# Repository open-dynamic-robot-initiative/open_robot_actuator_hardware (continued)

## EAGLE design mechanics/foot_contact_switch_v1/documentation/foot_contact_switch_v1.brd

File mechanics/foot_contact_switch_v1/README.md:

# Foot Contact Switch v1
 <br>*Working principle of the optical foot contact switch*

## Description
We designed simple, low cost, lightweight and robust optical foot contact switch for our [quadruped robot.](../quadruped_robot_8dof_v1#quadruped-robot-8dof-v1)  
The contact switch consists of a spring loaded aperture that is located between a led light source and a light sensor.  
External loads displace the aperture and change the light intensity measured by the sensor.  
For centering the foot we use 12 elastic silicone elements (6 on each side).

The foot contact switch is symmetric and can detect forces from a wide range of different angles (270 degrees).  
For visual feedback and monitoring there are bi-color leds mounted on each side of the foot.

<br>*Left side: Foot Contact Switch loaded / Right side: Foot Contact Switch unloaded*

## Lower Leg and Foot Contact Switch
 <br>*Lower Leg and Foot Contact Switch Component Overview*

 <br>*Lower Leg and Foot Contact Switch assembled - weight: 35g*

The weight of the foot, the contact switch electronics and the silicone elements is about 10g.  
To prevent the foot from rotating we use a steel pin that is guided by the lower leg structure.   
Under load the foot deflects up to 2mm from its neutral position.  
The electronics are supplied with 3.3V and generate an analog output signal between 3V and 0V.  
The signal is converted by the microcontroller ADC and transmitted over CAN at 1kHz.  
We measured the delay of the foot contact switch with respect to a ATI Mini40 force sensor for a drop of the 2dof leg from a height of 8cm.   
The measured delay between the ATI force sensor signal and the foot contact signal was 2ms.  
The data was logged at 1kHz using a Realtime Linux PC.

<br>*Foot Contact Switch Electronics*

## Video

## Sensor Characteristics
 <br>
* x-axis -> vertical force [N] measured with ATI Mini40 Sensor  
* y-axis -> foot contact sensor ouput signal inverted and normalized
* 0-1 on the y-axis corresponds to 3V - 0V range

## Off-the-shelf Components
### Silicone Tube
<br>

* Silicone tube - outer diameter: 6mm / inner diameter: 4mm / length: 3mm  
* 12 elements / 6 on each side
* a [tube cutter](../actuator_module_v1/details/details_tools.md#tube-cutter) can be used to prepare the segments

### Bicycle Tire
<br>

* a bicycle tire segment is bonded to the surface of the foot
* we use Schwalbe Lugano 28" 23-622 tire
* cut to 65mm x 10mm pieces
* bond to the foot with [Loctite 406](../actuator_module_v1/details/details_tools.md#loctite)
* [Instructions Foot Preparation](../general/lower_legs.md#preparing-the-lower-legs)

### Fasteners
<br>

* Steel Pin 1,5mm x 12mm  
* Socket Head Cap Screws M2,5x6
* Helicoil Thread Inserts M2,5 x 3.75mm

## 3D Printed Parts
 <br>

`The recommended printing direction for all the parts below is the positive z direction of the stl files.`

The STL files for 3d printing the parts are available in the [STL folder](stl_files).

 <br>
* [Lower Leg Structure Base - 18g](stl_files/lower_leg_structure_base.STL)
* FDM or SLS printer

 <br>
* [Lower Leg Structure Fork - 5g](stl_files/lower_leg_structure_fork.STL)
* FDM or SLS printer

 <br>
* [Foot Structure - 3.4g](stl_files/foot_structure.STL)
* SLA printer - Accura Extreme Gray

## Custom Electronic Boards
The foot contact switch consists of two boards with traces and components on all four sides.  
The diameter of the electronics boards is 10mm.  

 <br>*Foot Contact Switch Main Board  - Left: Outer side / Right: Inner Side*

 <br>*Foot Contact Switch Satellite Board  - Left: Outer side / Right: Inner Side*

## Light Sensor Offset
 <br>*Picture Light Sensor - the sensitive area is not in the center of the component*
* note that the sensing area of the light sensor is not in the geometrical center of the component
* when we solder the light sensor we use a microscope to align the sensing area of the sensor with the center of the board

## Switching Voltage for the Indicator Leds
 <br>*Schematic - voltage divider for switching the indicator leds*

* the switching voltage for the indicator leds on the foot is set by the voltage divider R4 and R5
* we use 10kΩ for R4 and 20kΩ for R5 resulting in a switching voltage of 2.2V
* you can adjust the switching voltage by changing the ratio of the voltage divider
* the switching voltage threshold is only used for the indicator leds
* the microcontroller receives the full range analog signal
* that means that you can set the threshold on the software side independently

## Details Foot Contact Switch
Special thanks to Joshi Walzog for designing and manufacturing the electronics boards!

* [Bill Of Materials Foot Contact Switch - PDF Document](documentation/bom_foot_contact_switch_v1.pdf)
* [Bill Of Materials - Excel Document](documentation/bom_foot_contact_switch_v1.xlsx)  
* [Eagle Files - Zipped Folder](documentation/eagle_files.zip)
* [Gerber Files - Zipped Folder](documentation/gerber_files.zip)

To view the Eagle files you need to download the free [Eagle PCB Design Software](https://www.autodesk.com/products/eagle/free-download#) for Windows, Mac and Linux.

## Foot Contact Switch Wiring
 <br>*Foot Contact Switch Connectors and Wiring*

## Alternative Lower Leg Versions

 <br>  

* alternative lower leg versions without contact sensor are documented here: [Lower Leg Documentation](../general/lower_legs.md#lower-legs)

## PDF Drawing
<br> *Foot Contact Switch Overview - Click on the picture to view the PDF drawing*

## View the foot contact switch cad model in your web browser
<br> *Foot Contact Switch - Click on the picture to view the cad model in your browser*

## More Information
[Open Dynamic Robot Initiative - Webpage](https://open-dynamic-robot-initiative.github.io)  
[Open Dynamic Robot Initiative - YouTube Channel](https://www.youtube.com/channel/UCx32JW2oIrax47Gjq8zNI-w)   
[Open Dynamic Robot Initiative - Forum](https://odri.discourse.group/categories)  
[Open Dynamic Robot Initiative - Paper](https://arxiv.org/pdf/1910.00093.pdf)  
[Hardware Overview](../../README.md#open-robot-actuator-hardware)  
[Software Overview](https://github.com/open-dynamic-robot-initiative/open-dynamic-robot-initiative.github.io/wiki)  

## Authors
Felix Grimminger

## License
BSD 3-Clause License

## Copyright
Copyright (c) 2019-2022, Max Planck Gesellschaft and New York University

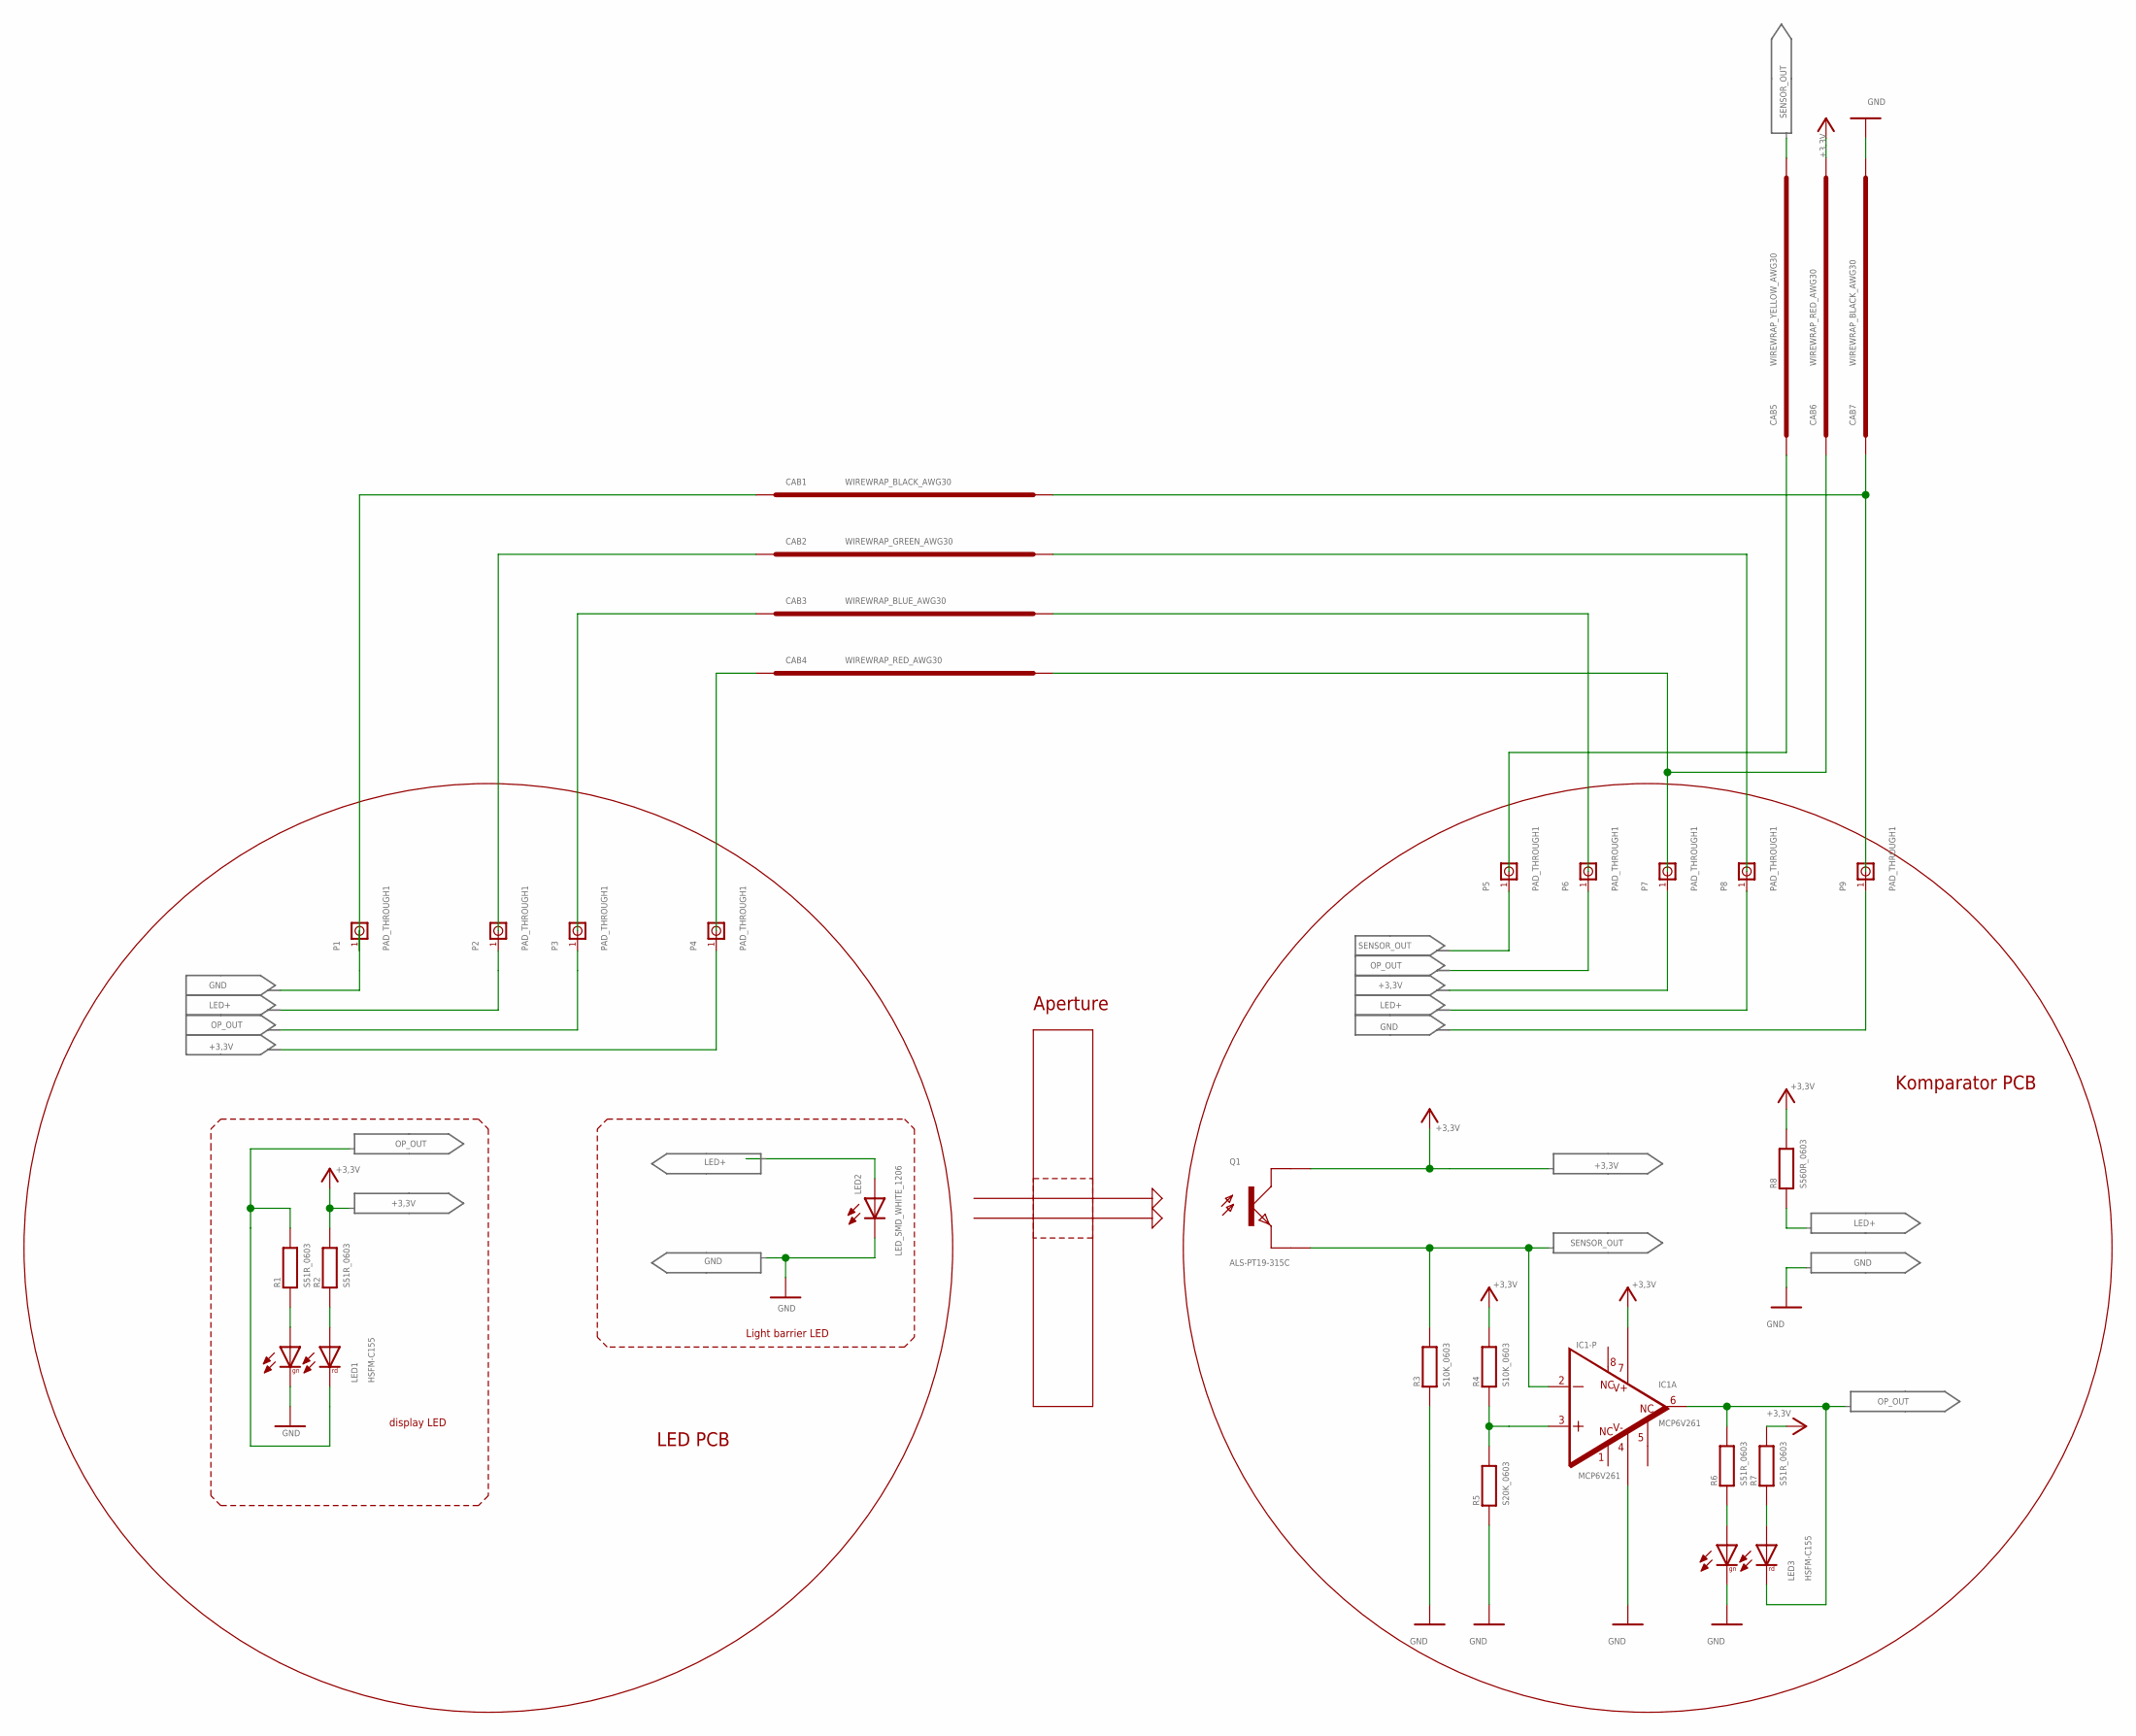
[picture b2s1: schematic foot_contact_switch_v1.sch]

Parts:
CAB1, CAB7: WIREWRAP_BLACK_AWG30; WIREWRAP_AWG30
CAB2: WIREWRAP_GREEN_AWG30; WIREWRAP_AWG30
CAB3: WIREWRAP_BLUE_AWG30; WIREWRAP_AWG30
CAB4, CAB6: WIREWRAP_RED_AWG30; WIREWRAP_AWG30
CAB5: WIREWRAP_YELLOW_AWG30; WIREWRAP_AWG30
IC1: MCP6V261; MSOP8
LED1, LED3: HSFM-C155; 3225
LED2: LED_SMD_WHITE_1206; 1206C
P1, P2, P3, P4, P5, P6, P7, P8, P9: PAD_THROUGH1; PAD_TH_056X055
Q1: ALS-PT19-315C; FOTOTRANSISTOR
R1, R2, R6, R7: S51R_0603; 0603R
R3, R4: S10K_0603; 0603R
R5: S20K_0603; 0603R
R8: S560R_0603; 0603R

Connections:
+3,3V: CAB6.7, IC1.7, P4.P$1, P7.P$1, Q1.1 (C), R2.P$2 (2), R4.P$2 (2), R7.P$2 (2), R8.P$2 (2)
GND: CAB7.7, IC1.4, LED1.2, LED2.- (C1), LED3.2, P1.P$1, P9.P$1, R3.P$1 (1), R5.P$1 (1)
LED+: LED2.+ (A1), P2.P$1, P8.P$1, R8.P$1 (1)
unnamed: IC1.3, R4.P$1 (1), R5.P$2 (2)
unnamed: CAB4.7, CAB6.1
unnamed: LED3.1, R6.P$1 (1)
unnamed: CAB1.7, CAB7.1
unnamed: LED3.3, R7.P$1 (1)
unnamed: LED1.1, R1.P$1 (1)
unnamed: LED1.3, R2.P$1 (1)
OP_OUT: IC1.6, LED1.4, LED3.4, P3.P$1, P6.P$1, R1.P$2 (2), R6.P$2 (2)
SENSOR_OUT: CAB5.7, IC1.2, P5.P$1, Q1.2 (E), R3.P$2 (2)

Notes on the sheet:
Aperture
LED PCB
Komparator PCB
display LED
Light barrier LED

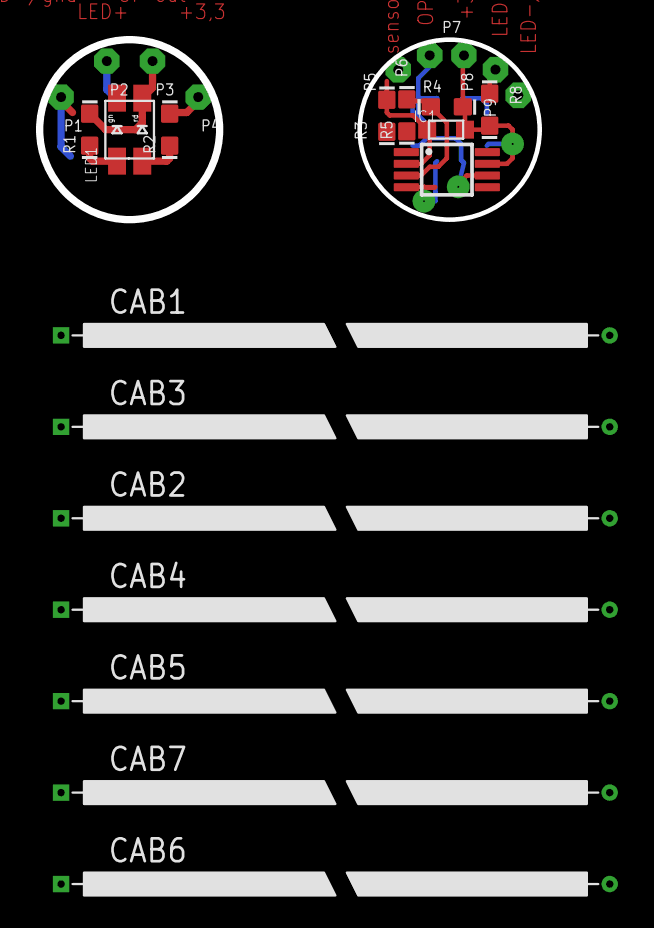
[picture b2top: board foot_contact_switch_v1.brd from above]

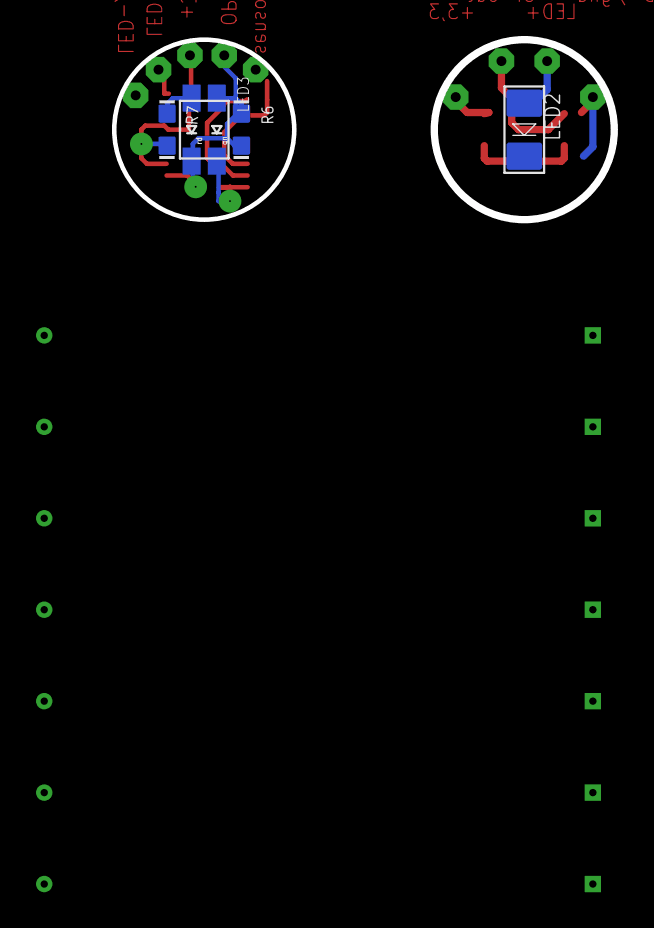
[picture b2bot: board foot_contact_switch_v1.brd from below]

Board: 2 copper layers, 29 parts (4 on the bottom side), 12 nets.

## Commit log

2019-08-20 Update LICENSE
2019-08-22 STL file upload
2019-09-03 Added actuator module description
2019-09-03 Updated documentation
2019-09-03 Update actuator module documentation
2019-09-04 Updating documentation
2019-09-10 Added detail information - 3d printed parts
2019-09-11 Updating documentation - print orientation 3d printed parts
2019-09-11 Updating 2dof leg documentation
2019-09-11 Updating documentation - foot contact switch
2019-09-12 Updating documentation - details actuator module
2019-09-12 Uploading technical drawings
2019-09-12 Updating documentation - machined parts
2019-09-12 Updating encoder codewheel documentation
2019-09-12 Fixing broken links
2019-09-18 Updating encoder documentation
2019-09-20 Updating wiring documentation
2019-09-30 Updating foot contact switch documentation
2019-09-30 Updating shell preparation and assembly documentation
2019-10-02 Adding video
2019-10-02 Uploading belt tensioner rollers different diameters
2019-10-02 Uploading tool for output pulley
2019-10-07 Updating lower leg documentation
2019-10-07 Fixing links
2019-10-08 Updating foot contact switch details
2019-10-08 Updating foot contact switch pictures
2019-10-10 Updating quadruped documentation
2019-10-10 Fixing link
2019-10-10 Fixing broken link
2019-10-10 Updating quadruped inertia parameters
2019-10-10 Linking cicle art video
2019-10-10 Uploading pictures
2019-10-21 Adding documentation - center pulley preparation
2019-10-21 Adding details - motor modification
2019-10-22 Updating documentation - center pulley preparation
2019-10-23 Adding tool documentation
2019-10-23 Adding detail pages - motor shaft and output pulley preparation
2019-10-24 Adding links to files
2019-10-25 Adding link to youtube channel
2019-10-30 Adding TI evaluation board information
2019-11-11 Updating tool documentation
2019-11-11 Adding Documentation - 3d printing orientation
2019-12-04 Added STL link for table attachment
2019-12-09 Adding documentation - simple lower leg
2019-12-13 Updating Micro Driver Documentation
2019-12-13 Updating MicroDriver documentation
2019-12-13 Basic outline for how to flash cards
2020-01-17 Adding pictures
2020-01-28 Adding documentation for udrive flashing
2020-01-28 Add German supplier for JTAG Emulator
2020-02-12 Uploading step files - machined parts
2020-02-12 Fixing broken links - software overview
2020-02-13 Adding images about jumper.
2020-02-13 Update the Flash the firmware part
2020-02-13 Upload images for CCS
2020-02-13 Import steps for running CSS debugger
2020-02-21 Testing
2020-02-21 Use markdown syntax for including images
2020-04-06 Adding links to encoder mount stl files
2020-04-27 Starting 12dof quadruped documentation
2020-04-28 Adding hip aa bearing information
2020-04-28 Uploading simplified Solo12 model for visualization
2020-05-04 Starting biped documentation
2020-05-04 Starting FingerEdu and TriFingerEdu documentation
2020-05-04 Documenting quadruped range of motion
2020-05-04 Updating navigation
2020-05-04 Removing duplicates
2020-05-06 Adding missing dimension
2020-05-08 Adding missing dimensions
2020-05-12 Uploading Hip AA Support Step File
2020-05-12 Uploading missing STL files
2020-05-12 Adding documentation - Body structure preparation and Vicon object
2020-05-13 Uploading step files
2020-05-19 Adding vicon object information for biped
2020-06-22 Updating documentation - electronic components
2020-06-24 Updating biped documentation
2020-06-24 Updating pictures
2020-06-26 Updating biped robot documentation
2020-06-26 Updating documentation - biped leg
2020-06-30 added stand_attachment FreeCAD model
    - not perfect reproduction of STL, some fillets are 0.5 instead of 1 mm
2020-07-02 Added FreeCAD CAD project files
    - body_structure_biped_right_side
    - micro_driver_stack_spacer
    Removed STL from stand_attachment
2020-07-06 Reinforcing electronics mount
2020-07-09 Updating documentation - leg test stand
2020-07-10 Updating footers
2020-07-16 Create iframe_test
2020-07-16 Update iframe_test
2020-07-16 Testing iFrame
2020-07-20 Updating documentation - bill of materials actuator module core
2020-07-21 Adding instructions for MicroDriver soldering
2020-07-21 Fix filenames
2020-07-22 MicroDriver: Rename image files
2020-07-24 Updating documentation - spi bus wiring
2020-07-24 Adding STL file - finger adapter
2020-07-28 added body_structure_biped_front freecad file
2020-08-03 Adding link to cad model for web browser
2020-08-03 Adding links to cad model for web browser
2020-08-03 Starting documentation - nyu finger
2020-08-05 Updating power connector ordering information
2020-08-10 Adding link- components and tools
2020-08-11 Updating sources for bearings
2020-08-12 Adding wiring documentation - Kabeltronik cables
2020-08-12 Moving shell stl files to 2dof leg
2020-08-12 Updating documentation - motor preparation
2020-08-13 Updating component information
2020-08-17 Updating drawings
2020-08-18 Updating documentation - encoder preparation
2020-08-18 Updating documentation - motor shaft preparation
2020-08-24 Updating documentation - step by step instructions
2020-08-26 Updating documentation - shell preparation
2020-08-31 Updating navigation - adding step by step instructions
2020-09-01 Updating codewheel ordering instructions
2020-09-21 Fixing view setting cad model
2020-09-30 Updating documentation - foot contact switch eagle and gerber files
2020-10-06 Uploading Solidworks files
2020-10-14 Updating step files
2020-10-15 Updating 8dof quadruped v2 documentation
2020-10-15 Updating docuementation
2020-10-16 Uploading wire edm drawings
2020-10-16 Replacing dxf file with zip file
2020-10-19 Uploading vicon top structure quadruped 8dof v2
2020-10-19 Uploading Solidworks files quadruped 8dof v1
2020-10-19 Uploading edrawing files
2020-10-20 Linking cad models for viewing in browser
2020-10-21 Updating documentation - quadruped 8dof v2 vicon object
2020-10-22 Updating documentation - quadruped 8dof v2
2020-10-26 Update documentation
2020-10-28 Correcting error in upper leg shell cover
2020-10-30 Updating documentation - 3dof leg
2020-11-25 Fixing navigation
2020-11-25 Updating documtentation
2020-11-25 added the alternative option for the 3d printed encoder codewheel
2020-11-25 Adding wiring documentation - 12dof quadruped
2020-11-27 Updating documentation - 12dof robot
2020-12-02 Update README.md
    Fixing a broken link to the Transmission Belt Tensioner Roller.
2020-12-03 Updating conventions
2020-12-11 Fixing broken links to stl parts
2021-01-15 Adding details to the actuator module assembly instructions
2021-01-18 added link for precision resistors
2021-01-20 Updating component and tool information
2021-01-22 Updating TI evaluation board documentation
2021-01-22 Adding STL file body structure bottom Rev A
2021-01-26 Updating the micro driver documentation
2021-02-05 Adding robot calibration page
2021-02-09 Adding lower leg documentation page
2021-02-09 added input voltage for motor board
    please check if the added description is correct
2021-02-11 Updating navigation - linking lower legs and robot calibration pages
2021-02-11 Replacing outdated upper leg structure
2021-02-11 Updating lower leg versions
2021-02-11 Updating biped body structure top - adding STL files with IMU attachment
2021-02-12 fixed typo
2021-02-17 Adding Biped Calibration Tool Documentation
2021-02-18 Adding battery documentation
2021-02-23 Documenting robot origins and inertial sensor origin positions
2021-02-24 added LED status of motor board to readme
2021-02-25 Uploading Solidworks Files - Leg Test Stand v1
    Solidworks 2017
2021-02-25 Uploading Solidworks Files - Dual Motor Testbed
    Solidworks 2017
2021-02-25 Uploading Solidworks Files - NYU Finger
    Solidworks 2017
2021-02-25 Uploading Solidworks Files - TriFinger Edu v1
    Solidworks 2017
2021-02-25 Uploading Solidworks Files - Biped 6dof v1
    Solidworks 2017
2021-02-25 Updating Solidworks Files - Quadruped 8dof v1
    Solidworks 2017
2021-02-25 Updating Solidworks Files - Quadruped 8dof v2
    Solidworks 2017
2021-02-25 Updating Solidworks Files - Quadruped 12dof v1
    Solidworks 2017
2021-02-25 Updating Solidworks Files - Foot Contact Switch v1
    Solidworks 2017
2021-02-26 Updating html cad links
2021-03-18 Adding roll bar to quadruped 8dof v2 body structure top
2021-03-18 Adding ordering information - robot push button switches
2021-03-18 Updating documentation - helicoil ordering information
2021-03-23 Updating picture
2021-03-26 Starting Quadruped 12dof v1.1 documentation - autonomy upgrade
2021-04-09 Uploading odri encoder kit product flyer
2021-04-14 Starting Actuator Module Core v1.1 documentation
2021-04-26 Updating documentation - biped stack assignment
2021-04-27 Updating documentation - Leg Test Stand v1
2021-04-27 Correcting link to solidworks files
2021-04-27 Updating navigation
    Adding Actuator Module Core v1.1 and Leg Test Stand v2
2021-04-27 Starting Leg Test Stand v2 documentation
2021-04-27 Updating navigation - adding Actuator Module Core v1.1 and Leg Test Stand v2
2021-05-03 Updating Leg Test Stand documentation
2021-05-06 Updating Biped Leg 3dof documentation
2021-05-07 Updating Biped Leg documentation
2021-05-18 Updating Link - Power Board Documentation
2021-05-18 Updating Finger Edu Documentation
2021-05-19 Update README.md
    added link to the odri forum about how to use a different imu
2021-05-20 Updating Quadruped 12dof - Hip AA Support Rev A
    The height of the internal wire passage was increased - from 4mm to 7mm.
2021-06-11 Updating Quadruped Robot 12dof documentation
2021-06-14 Adding Link - imu wiring documentation
2021-06-16 Updating Leg 3dof v1 Documentation
2021-07-09 Adding Solo12 commercial option - PAL Robotics
2021-08-23 Adding Alternative Version - Hip FE Module Shell Base
2021-08-31 Adding Wiring Documentation - Quadruped 12dof v1.1
2021-09-06 Update details_motor_preparation.md
    It is better to warn of this step before the step is shown to prevent mistakes.
2021-09-10 Updating documentation - earlier warning - don't shorten hip aa motor phase wires
2021-09-10 Updating documentation - stand for quadruped robot
2022-03-07 Adding STL file - tool output pulley modification
2022-04-05 Updating JTAG emulator ordering information
2022-04-13 Uploading Solidworks Files - Quadruped Robot 12dof v1.1
2022-08-15 Uploading Biped 6dof v1 STEP files
2022-08-16 Updating Solo12 STL files for visualization
2022-08-16 Updating quadruped 12dof v1 inertia parameter documentation
2022-08-17 Uploading inertia documentation and simplified STL files for the quadruped robot 8dof v2
